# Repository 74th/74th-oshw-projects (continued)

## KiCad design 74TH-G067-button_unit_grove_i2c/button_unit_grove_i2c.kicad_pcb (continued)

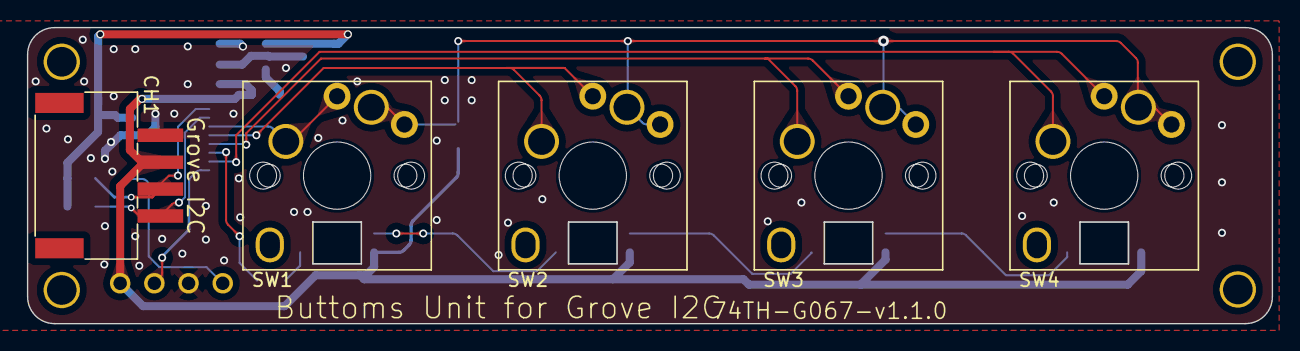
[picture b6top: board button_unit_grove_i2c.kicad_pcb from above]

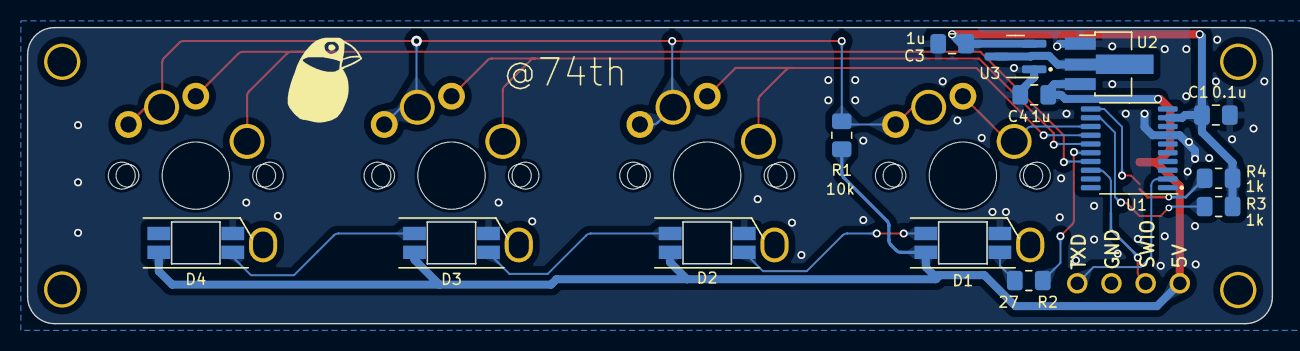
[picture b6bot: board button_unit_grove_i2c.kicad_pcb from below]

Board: 2 copper layers, 92.5 x 22.0 mm, 25 parts (15 on the bottom side), 18 nets.

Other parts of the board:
M2-1, M2-1#2, M2-1#3, M2-1#4: M2_v2
MISC-ICON: LOGO; Logo_74th_7.5mm

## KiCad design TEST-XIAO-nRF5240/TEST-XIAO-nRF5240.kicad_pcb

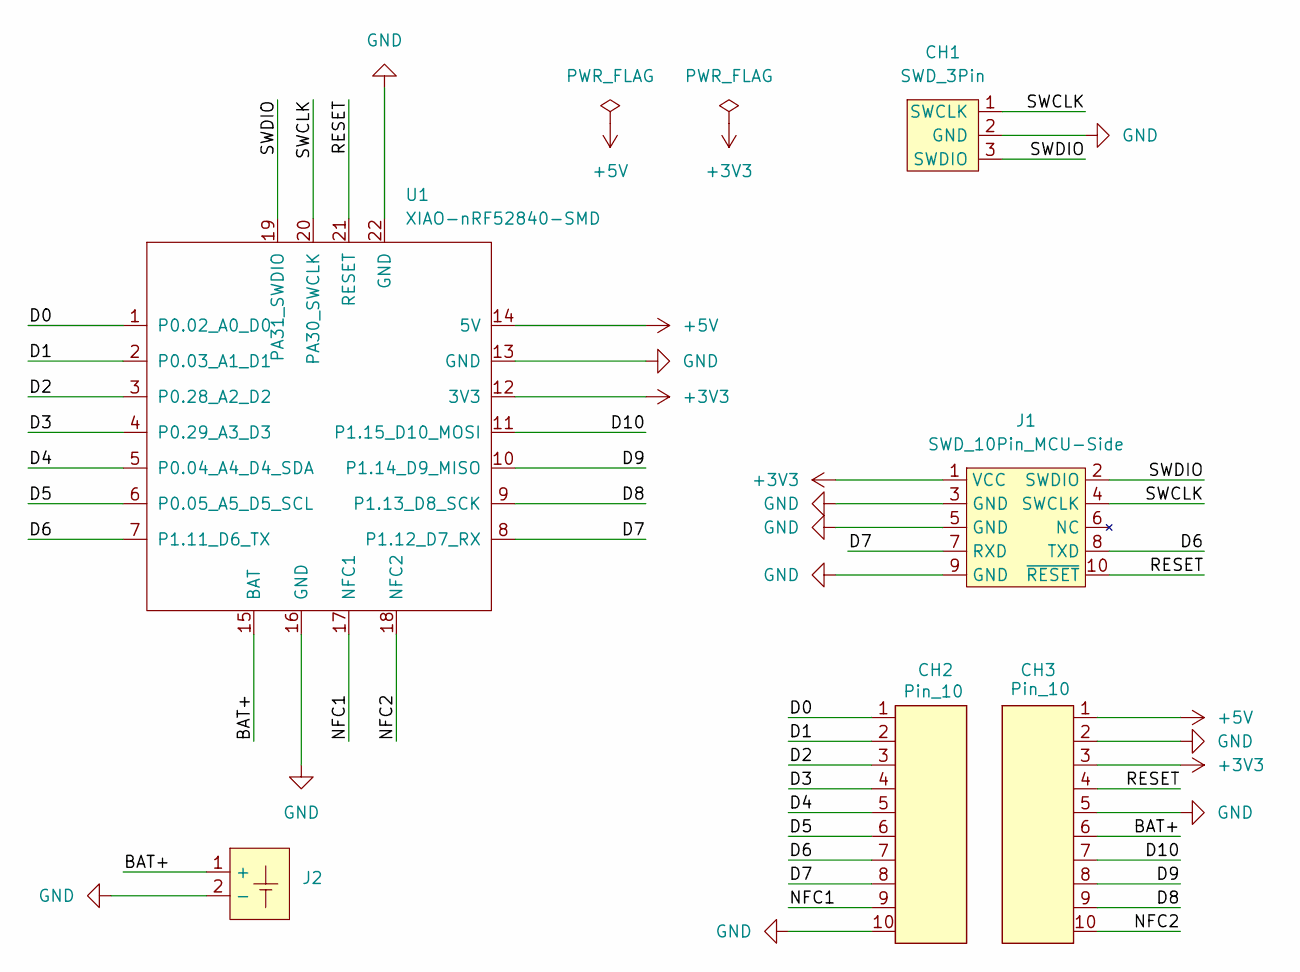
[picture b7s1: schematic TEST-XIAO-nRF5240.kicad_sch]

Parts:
CH1: SWD_3Pin; PinOut_Pin_3_2GND
CH2, CH3: Pin_10; PinOut_Pin_10
J1: SWD_10Pin_MCU-Side; Connector_HalfPinHeader_SWD
J2: JST_PH_B2B-PH-K_1x02_P2.00mm_Vertical
U1: XIAO-nRF52840-SMD

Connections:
+3V3: CH3.3, J1.1 (VCC), U1.12 (3V3)
+5V: CH3.1, U1.14 (5V)
/BAT+: CH3.6, J2.1 (+), U1.15 (BAT)
/D0: CH2.1, U1.1 (P0.02_A0_D0)
/D1: CH2.2, U1.2 (P0.03_A1_D1)
/D2: CH2.3, U1.3 (P0.28_A2_D2)
/D3: CH2.4, U1.4 (P0.29_A3_D3)
/D4: CH2.5, U1.5 (P0.04_A4_D4_SDA)
/D5: CH2.6, U1.6 (P0.05_A5_D5_SCL)
/D6: CH2.7, J1.8 (TXD), U1.7 (P1.11_D6_TX)
/D7: CH2.8, J1.7 (RXD), U1.8 (P1.12_D7_RX)
/D8: CH3.9, U1.9 (P1.13_D8_SCK)
/D9: CH3.8, U1.10 (P1.14_D9_MISO)
/D10: CH3.7, U1.11 (P1.15_D10_MOSI)
/NFC1: CH2.9, U1.17 (NFC1)
/NFC2: CH3.10, U1.18 (NFC2)
/RESET: CH3.4, J1.10 (~RESET), U1.21 (RESET)
/SWCLK: CH1.1 (SWCLK), J1.4 (SWCLK), U1.20 (PA30_SWCLK)
/SWDIO: CH1.3 (SWDIO), J1.2 (SWDIO), U1.19 (PA31_SWDIO)
GND: CH1.2 (GND), CH2.10, CH3.2, CH3.5, J1.3 (GND), J1.5 (GND), J1.9 (GND), J2.2 (-), U1.13 (GND), U1.16 (GND), U1.22 (GND)

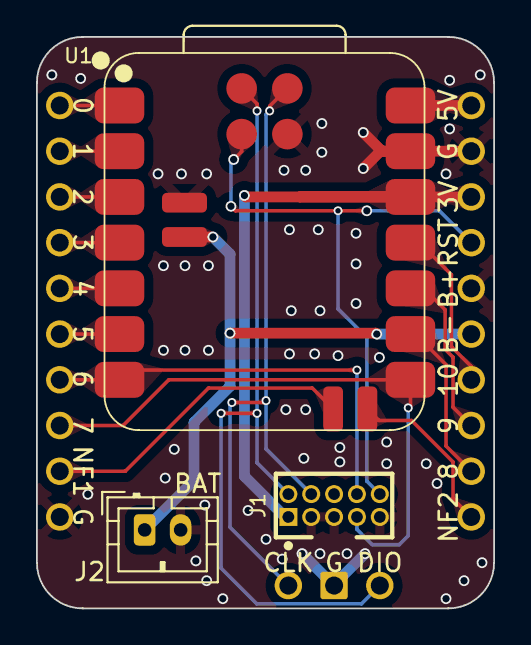
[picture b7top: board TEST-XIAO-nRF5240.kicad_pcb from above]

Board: 2 copper layers, 25.4 x 31.8 mm, 7 parts (1 on the bottom side), 20 nets.

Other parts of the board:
MISC-ICON: LOGO; Logo_74th_5mm

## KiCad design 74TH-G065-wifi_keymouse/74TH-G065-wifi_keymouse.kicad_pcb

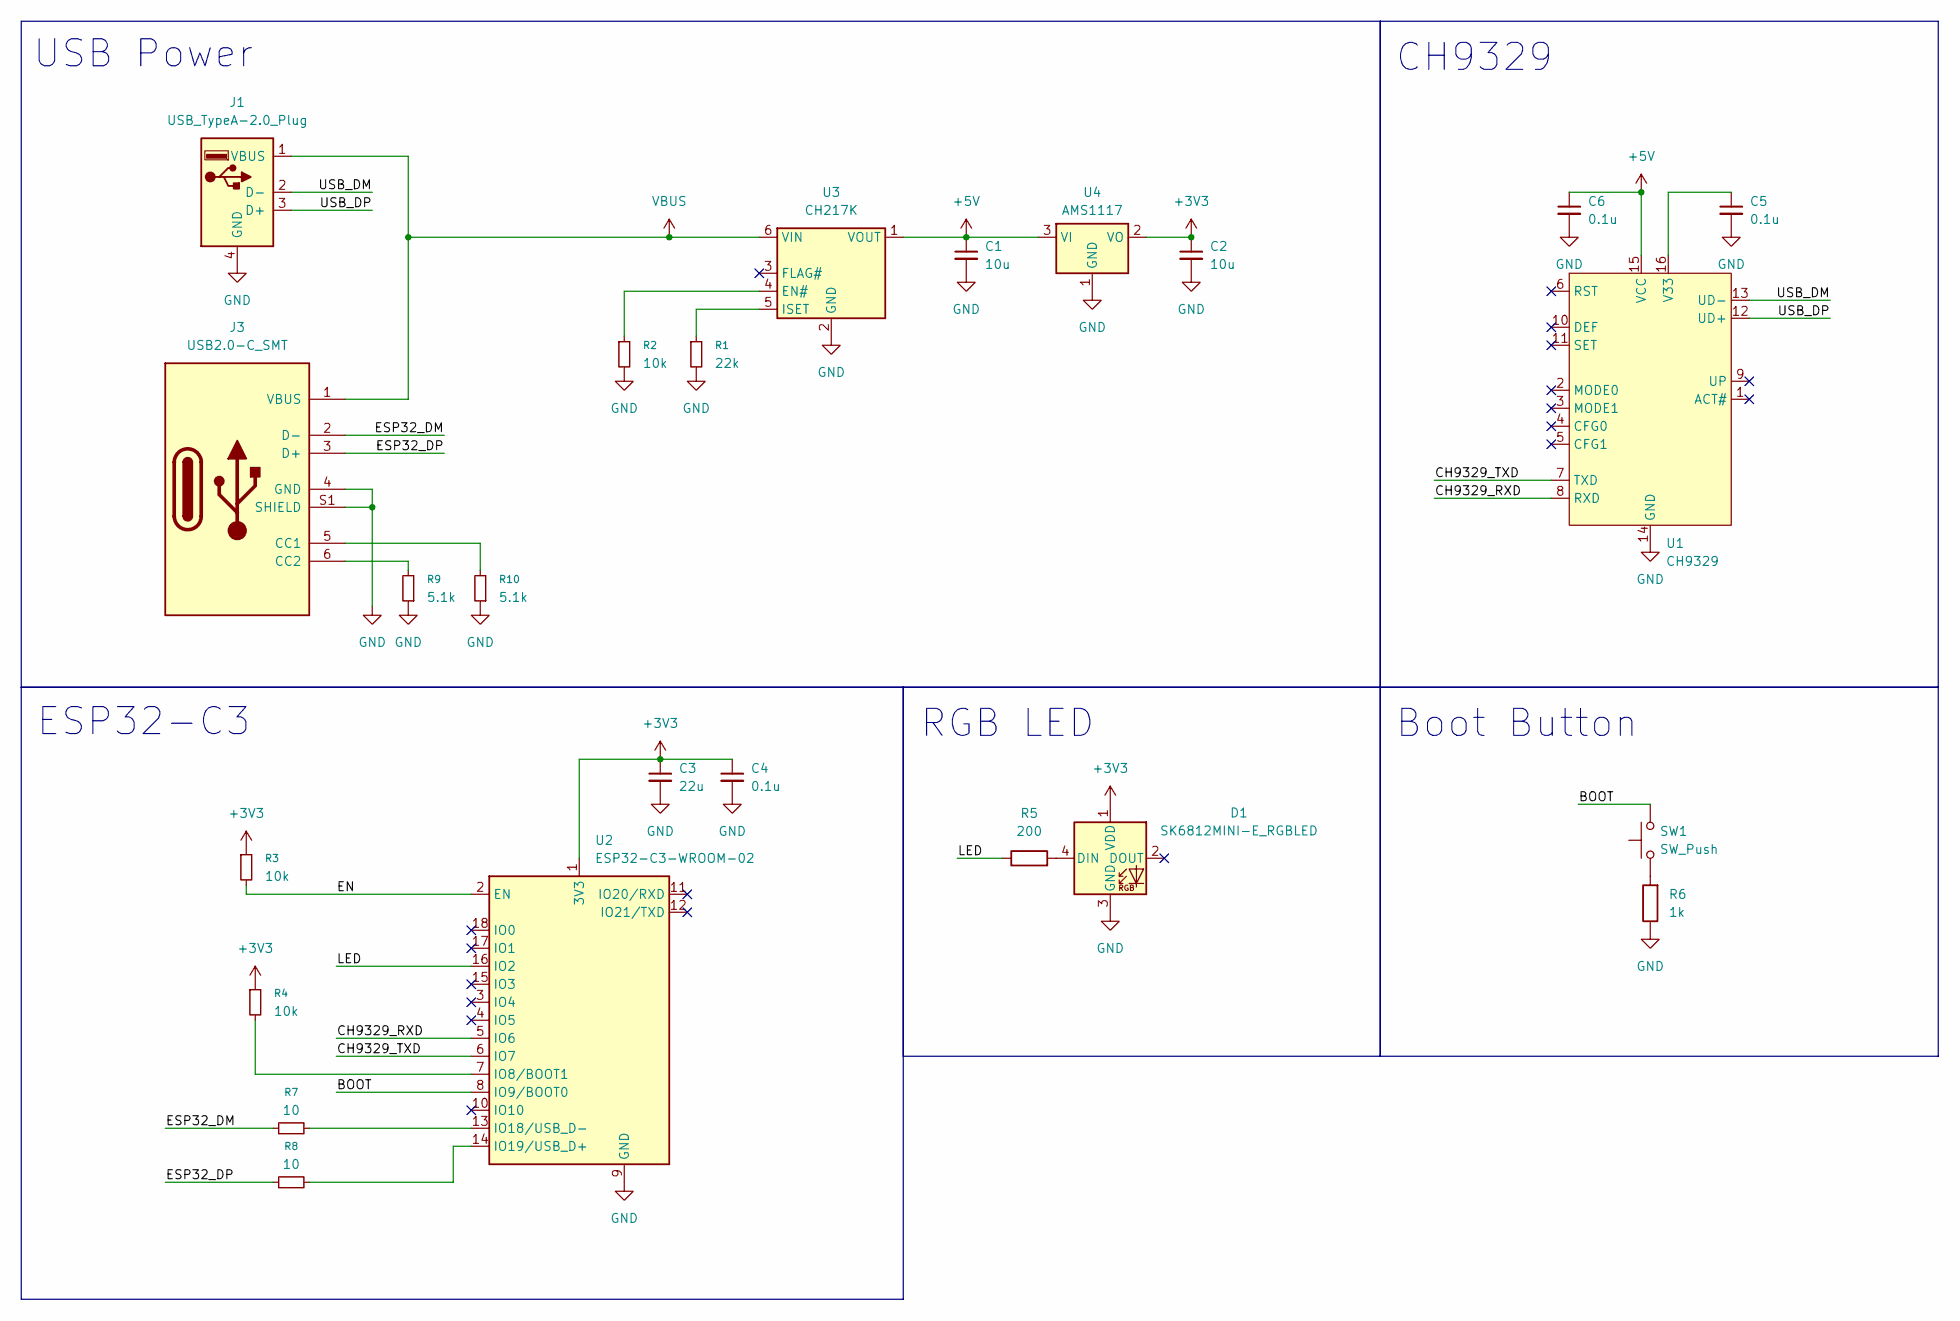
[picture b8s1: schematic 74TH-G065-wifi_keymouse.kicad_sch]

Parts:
C1, C2: 10u; Capacitor_0603_1608
C3: 22u; Capacitor_0603_1608
C4, C5, C6: 0.1u; Capacitor_0603_1608
D1: SK6812MINI-E_RGBLED; LED_SK6812MINI-E_BACK-RIGHT
J1: USB_TypeA-2.0_Plug; Connector_USB-A-Plug_TH
J3: USB2.0-C_SMT; Connector_USB-C-Receptacle_SMT_12-Pin_Simple
R1: 22k; Register_0603_1608
R2, R3, R4: 10k; Register_0603_1608
R5: 200; Register_0603_1608
R6: 1k; Register_0603_1608
R7, R8: 10; Register_0603_1608
R9, R10: 5.1k; Register_0603_1608
SW1: SW_Push; Switch_SKRPABE010
U1: CH9329; SOP-16_3.9x9.9mm_P1.27mm
U2: ESP32-C3-WROOM-02; Module_ESP32-C3-WROOM-02
U3: CH217K; Package_SOT-23-6
U4: AMS1117; Package_SOT-89-3

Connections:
+3V3: C2.1, C3.1, C4.1, D1.1 (VDD), R3.1, R4.1, U2.1 (3V3), U4.2 (VO)
+5V: C1.1, C6.1, U1.15 (VCC), U3.1 (VOUT), U4.3 (VI)
/BOOT: SW1.2, U2.8 (IO9/BOOT0)
/CH9329_RXD: U1.8 (RXD), U2.5 (IO6)
/CH9329_TXD: U1.7 (TXD), U2.6 (IO7)
/EN: R3.2, U2.2 (EN)
/ESP32_DM: J3.2 (D-), R7.1
/ESP32_DP: J3.3 (D+), R8.1
/LED: R5.1, U2.16 (IO2)
/USB_DM: J1.2 (D-), U1.13 (UD-)
/USB_DP: J1.3 (D+), U1.12 (UD+)
GND: C1.2, C2.2, C3.2, C4.2, C5.2, C6.2, D1.3 (GND), J1.4 (GND), J3.4 (GND), J3.S1 (SHIELD), R1.2, R2.2, R6.1, R9.1, R10.1, U1.14 (GND), U2.9 (GND), U2.19 (GND), U3.2 (GND), U4.1 (GND)
unnamed: D1.4 (DIN), R5.2
unnamed: J3.5 (CC1), R10.2
unnamed: J3.6 (CC2), R9.2
unnamed: R6.2, SW1.1
unnamed: C5.1, U1.16 (V33)
unnamed: R4.2, U2.7 (IO8/BOOT1)
unnamed: R7.2, U2.13 (IO18/USB_D-)
unnamed: R8.2, U2.14 (IO19/USB_D+)
unnamed: R2.1, U3.4 (EN#)
unnamed: R1.1, U3.5 (ISET)
VBUS: J1.1 (VBUS), J3.1 (VBUS), U3.6 (VIN)

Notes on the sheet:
CH9329
Boot Button
ESP32-C3
RGB LED
USB Power

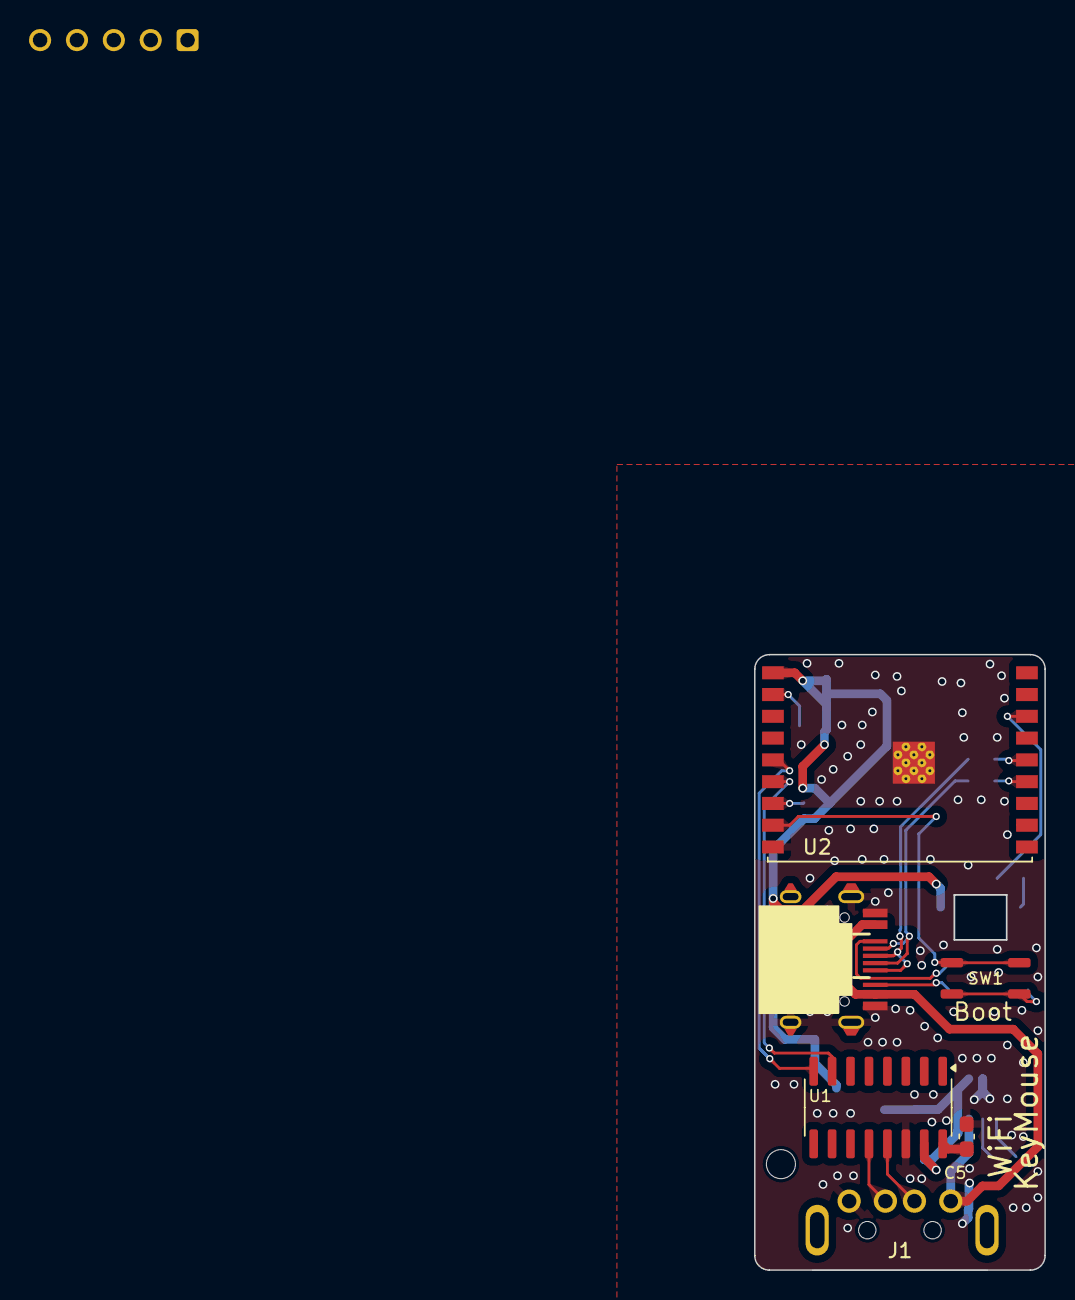
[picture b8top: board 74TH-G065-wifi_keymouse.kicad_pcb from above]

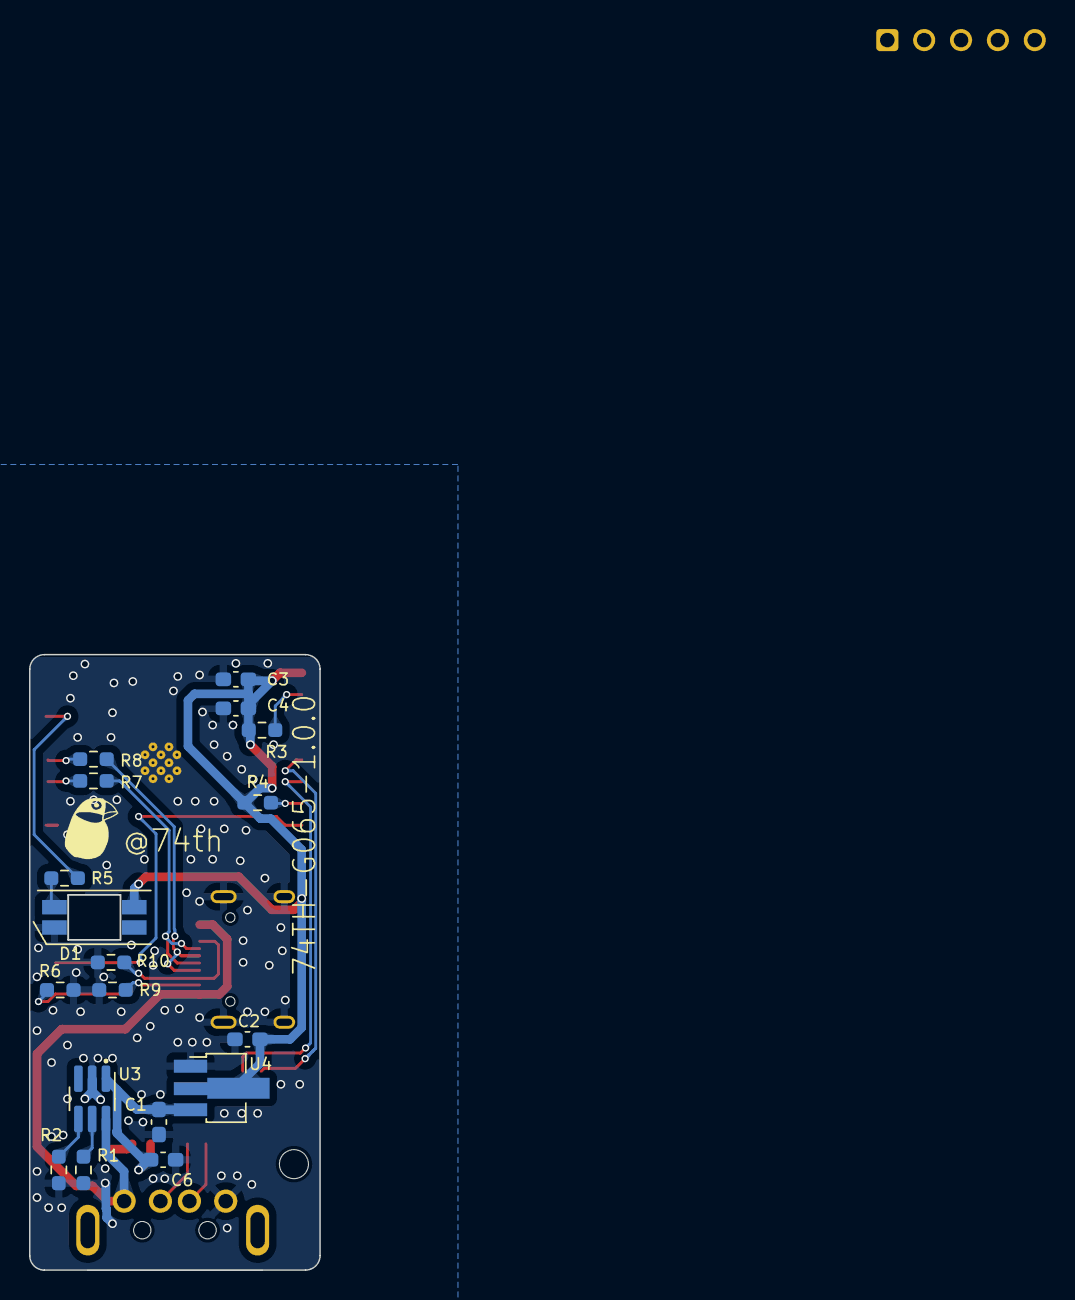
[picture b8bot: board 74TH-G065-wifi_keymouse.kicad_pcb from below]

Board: 2 copper layers, 20.0 x 42.4 mm, 27 parts (19 on the bottom side), 23 nets.

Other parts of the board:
CH1: Pin_5; PinOut_Pin_5_GND
M2: Hole_M2_2.0
MISC-ICON: LOGO; Logo_74th_5mm

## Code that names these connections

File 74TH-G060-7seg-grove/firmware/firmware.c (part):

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#include <stdio.h>
#include <stdbool.h>

#define LED_A_PIN PC4  // 7SEG 7
#define LED_B_PIN PC3  // 7SEG 6
#define LED_C_PIN PD3  // 7SEG 4
#define LED_D_PIN PD2  // 7SEG 2
#define LED_E_PIN PC7  // 7SEG 1
#define LED_F_PIN PC5  // 7SEG 9
#define LED_G_PIN PC6  // 7SEG 10
#define LED_DP_PIN PA1 // 7SEG 5
#define SEL1_PIN PD6
#define SEL2_PIN PD5
#define SEL3_PIN PD4
#define SEL4_PIN PC0

#define COMM_LED_PIN PA2

#define SEGPATTERN_0 0b00111111
#define SEGPATTERN_1 0b00000110
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#define DEMO_MODE 0

uint16_t LED_PINS[MODULE_LED_NUM] = {LED_A_PIN, LED_B_PIN, LED_C_PIN, LED_D_PIN, LED_E_PIN, LED_F_PIN, LED_G_PIN, LED_DP_PIN};
uint16_t SEL_PINS[MODULE_NUM] = {SEL1_PIN, SEL2_PIN, SEL3_PIN, SEL4_PIN};

volatile uint8_t i2c_registers[32] = {0x00};
volatile uint8_t i2c_registers_prev[32] = {0x00};
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{
	// https://github.com/cnlohr/ch32v003fun/blob/master/examples/i2c_slave/i2c_slave.h

	// PC1 is SDA, 10MHz Output, alt func, open-drain
	GPIOC->CFGLR &= ~(0xf << (4 * 1));
	GPIOC->CFGLR |= (GPIO_Speed_10MHz | GPIO_CNF_OUT_OD_AF) << (4 * 1);

	// PC2 is SCL, 10MHz Output, alt func, open-drain
	GPIOC->CFGLR &= ~(0xf << (4 * 2));
	GPIOC->CFGLR |= (GPIO_Speed_10MHz | GPIO_CNF_OUT_OD_AF) << (4 * 2);

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
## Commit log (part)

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2024-05-11 init
2024-05-12 grove-qwiic-bb-bridge
2024-05-13 grove_qwiic_bb_bridge/v1.0.0
2024-05-17 lipo-dcdc-testing
2024-06-03 grove_qwiic_bb_bridge/v1.0.1
2024-06-10 grove_universal_board/v1.0.0
2024-06-10 grove_qwiic_debug_adapter/v1.0.0
2024-06-11 grove_universal_board/v1.1.0
2024-07-08 smd to th
2024-07-19 first
2024-07-20 usb-adapter-amcf/1.0.0
2024-07-20 usb-adapter-mmcf/1.0.0
2024-07-20 usb switch adapter
2024-07-21 add photo
2024-07-21 add conv3
2024-07-21 usb-switch-adapter/1.0.0
2024-07-22 usb-adapter-mmcf/1.0.1
2024-07-28 usb-adapter-mmcf-l/1.0.0
2024-08-04 create project
2024-08-04 create switch
2024-08-05 overcurrent, led
2024-08-05 usb-switch-adapter/1.1.0
2024-08-07 grove-keymouse/1.0.0
2024-08-07 ディレクトリ構成変更
2024-08-17 update Document
2024-09-15 Grove KeyMouse
2024-10-27 diy-cable-checker
2024-11-11 add firmware
2024-11-16 firmware binary
2024-11-16 cable checker
2024-12-07 copy from ch32v003fun
2024-12-08 7seg-grove/1.0.0
2024-12-08 usb_adapter_micro-male_to_c-female/1.0.0
2024-12-08 1.0.0
2024-12-19 fix pins
2024-12-19 arduino sample
2024-12-19 uint16 input
2024-12-19 sample
2024-12-19 fix afterimage
2024-12-20 replace position
2024-12-20 us -> tick
2024-12-20 firmware build
2024-12-21 point
2024-12-21 firmware uploader
2024-12-21 add documents
2024-12-22 update sample
2024-12-29 small fix
2024-12-29 Grove Expander
2025-04-27 wifi keymouse: minimal
2025-04-29 wifi_keymouse/1.0.0
2025-05-11 TEST-XIAO-nRF5240/1.0.0
2025-11-22 button_unit_grove_i2c,1Key_CH32V003
2026-02-06 add case
2026-02-07 update case
2026-02-22 grove-uart-adapter/1.0.0
2026-02-22 usb_power_adapter/1.0.0
2026-03-20 74TH-G073-m5atom_breakout/1.0.0
2026-03-20 74TH-G074-M5_Core_port_bottom/1.0.0
2026-03-20 74TH-G071-grove_uart_usb_adapter/1.1.0
2026-03-30 74TH-G074-M5_Core_port_bottom/1.0.1
